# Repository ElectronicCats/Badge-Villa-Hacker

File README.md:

# La Villa Hacker 2025 Badge

## Technology

- CH32V003
- NRF24L01
- Display OLED
- 2x AAA Battery Holder
- Shitty Addon Connector

## Getting Started

Your badge comes with a pre-installed firmware, but in case you need to reprogram it, you can use the binaries from the release section.

If you want to build your own firmware, check out the [README](firmware/README.md) in the firmware folder.

## Gratitude
Do you want to say thank you? Tag these companies on social networks and show them your badge, thanks to them it is possible

- [Electronic Cats](https://electroniccats.com/)

## License

Electronic Cats invests time and resources providing this open source design, please support Electronic Cats and open-source hardware by purchasing products from Electronic Cats!

Designed by Electronic Cats.

Hardware released under an CERN Open Hardware Licence v1.2. See the LICENSE_HARDWARE file for more information.

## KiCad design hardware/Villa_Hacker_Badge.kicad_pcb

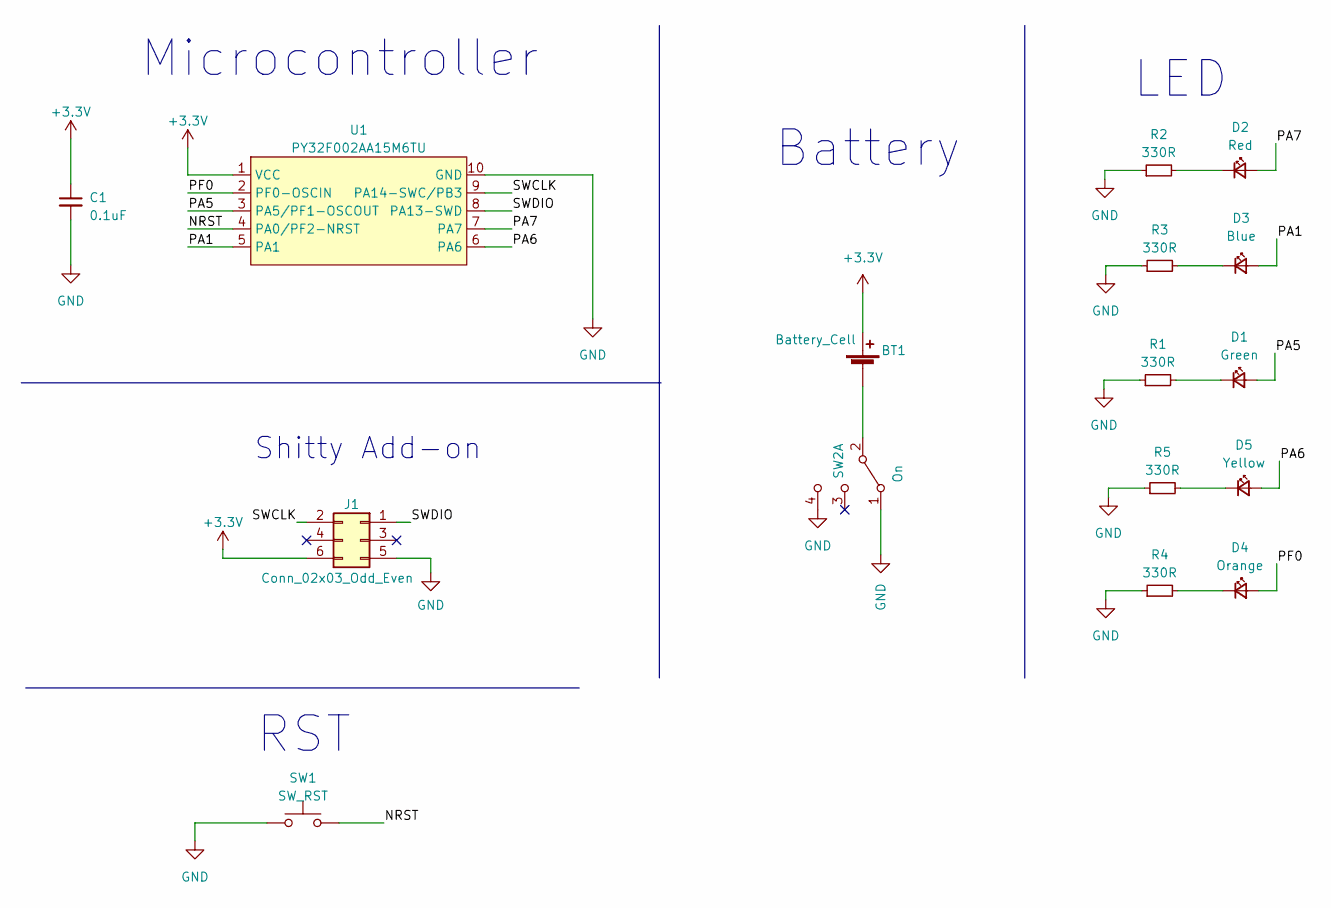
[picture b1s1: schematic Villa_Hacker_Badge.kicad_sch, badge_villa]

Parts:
BT1: Battery_Cell; BAT-HLD-001; LCSC# C964833
C1: 0.1uF; C_0805_2012Metric; LCSC# C235731
D1: Green; LED_0805_2012Metric; LCSC# C965815
D2: Red; LED_0805_2012Metric; LCSC# C965812
D3: Blue; LED_0805_2012Metric; LCSC# C205441
D4: Orange; LED_0805_2012Metric; LCSC# C434437
D5: Yellow; LED_0805_2012Metric; LCSC# C84261
J1: Conn_02x03_Odd_Even; PinHeader_2x03_P2.54mm_Vertical; LCSC# C706893
R1, R2, R3, R4, R5: 330R; R_0805_2012Metric; LCSC# C119075
SW1: SW_RST; SW_SPST_TL3342; LCSC# C318889
SW2: On; MSK12C02; LCSC# C431540
U1: PY32F002AA15M6TU; PY32F002AA15M; LCSC# C5292058

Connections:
+3.3V: BT1.2 (+), C1.1, J1.6, U1.1 (VCC)
/NRST: SW1.2, U1.4 (PA0/PF2-NRST)
/PA1: D3.2 (A), U1.5 (PA1)
/PA5: D1.2 (A), U1.3 (PA5/PF1-OSCOUT)
/PA6: D5.2 (A), U1.6 (PA6)
/PA7: D2.2 (A), U1.7 (PA7)
/PF0: D4.2 (A), U1.2 (PF0-OSCIN)
/SWCLK: J1.2, U1.9 (PA14-SWC/PB3)
/SWDIO: J1.1, U1.8 (PA13-SWD)
GND: C1.2, J1.5, R1.1, R2.1, R3.1, R4.1, R5.1, SW1.1, SW2.1 (A), SW2.4 (C), U1.10 (GND)
unnamed: BT1.1 (-), SW2.2 (B)
unnamed: D1.1 (K), R1.2
unnamed: D2.1 (K), R2.2
unnamed: D3.1 (K), R3.2
unnamed: D4.1 (K), R4.2
unnamed: D5.1 (K), R5.2

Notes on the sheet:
Shitty Add-on
Battery
Microcontroller
LED
RST

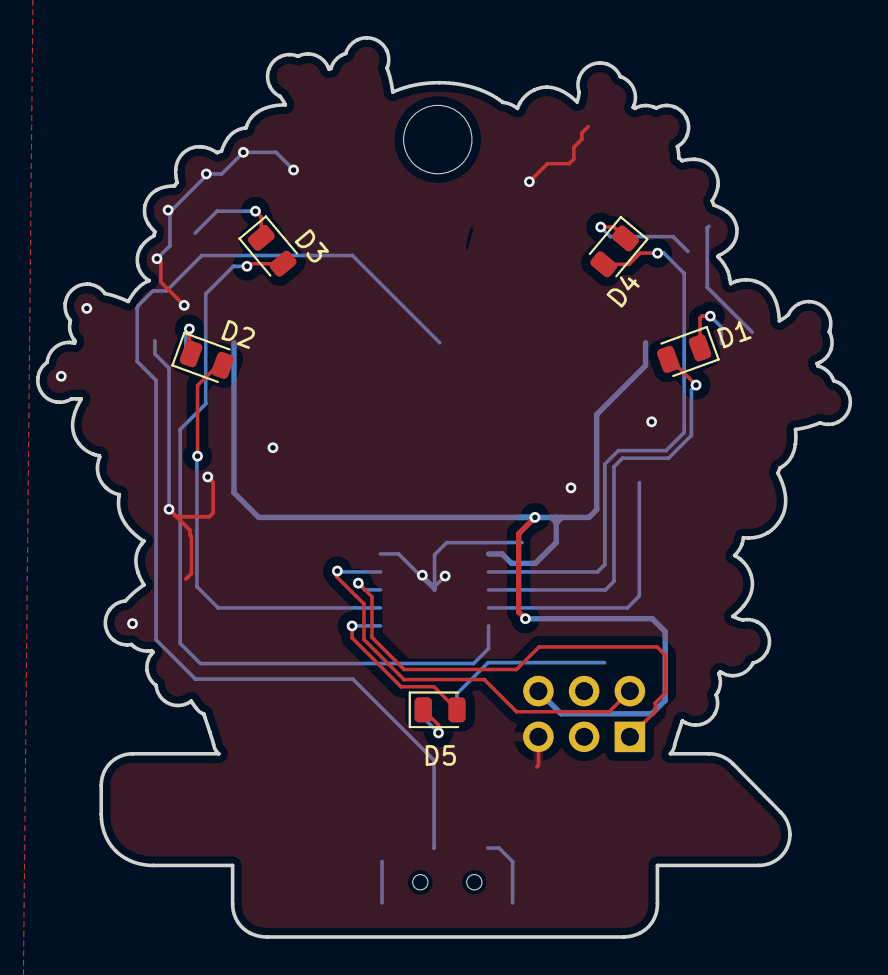
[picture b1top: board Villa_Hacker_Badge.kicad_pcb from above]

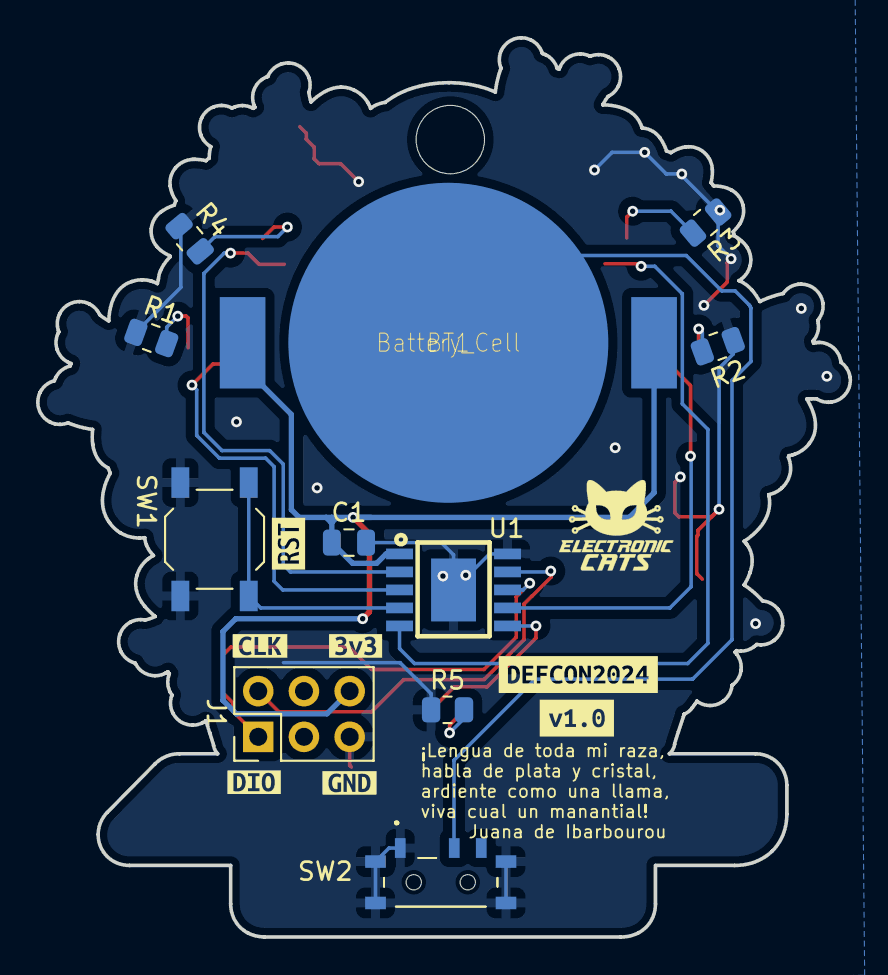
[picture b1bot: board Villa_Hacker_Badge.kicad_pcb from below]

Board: 2 copper layers, 45.1 x 50.0 mm, 23 parts (18 on the bottom side), 16 nets.

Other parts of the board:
kibuzzard-6685D235: G***; kibuzzard-6685D235
kibuzzard-66857BF8: G***; kibuzzard-66857BF8
kibuzzard-66857C28: G***; kibuzzard-66857C28
kibuzzard-668588B5: G***; kibuzzard-668588B5
kibuzzard-6685884A: G***; kibuzzard-6685884A
kibuzzard-66858654: G***; kibuzzard-66858654
kibuzzard-66858661: G***; kibuzzard-66858661

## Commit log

2024-07-03 feat(Hw):First_Route
2024-07-03 feat(Hw):Added_details
2024-07-03 feat(hw): add labels and logos
2024-07-03 fix (hw): update #LCSC orange LED
2024-07-03 feat(Hw):Add_Hole
2024-07-03 fix(Hw):Move_Switch
2024-07-03 fix(Hw):Moved_F.Mask
2024-07-03 fix(hw): logo EC
2024-07-18 feat(fw): Add firmware
2025-06-25 feat(hw): remove zones
2025-09-18 docs:Update README.md
2025-09-18 fix: typo Update README.md
